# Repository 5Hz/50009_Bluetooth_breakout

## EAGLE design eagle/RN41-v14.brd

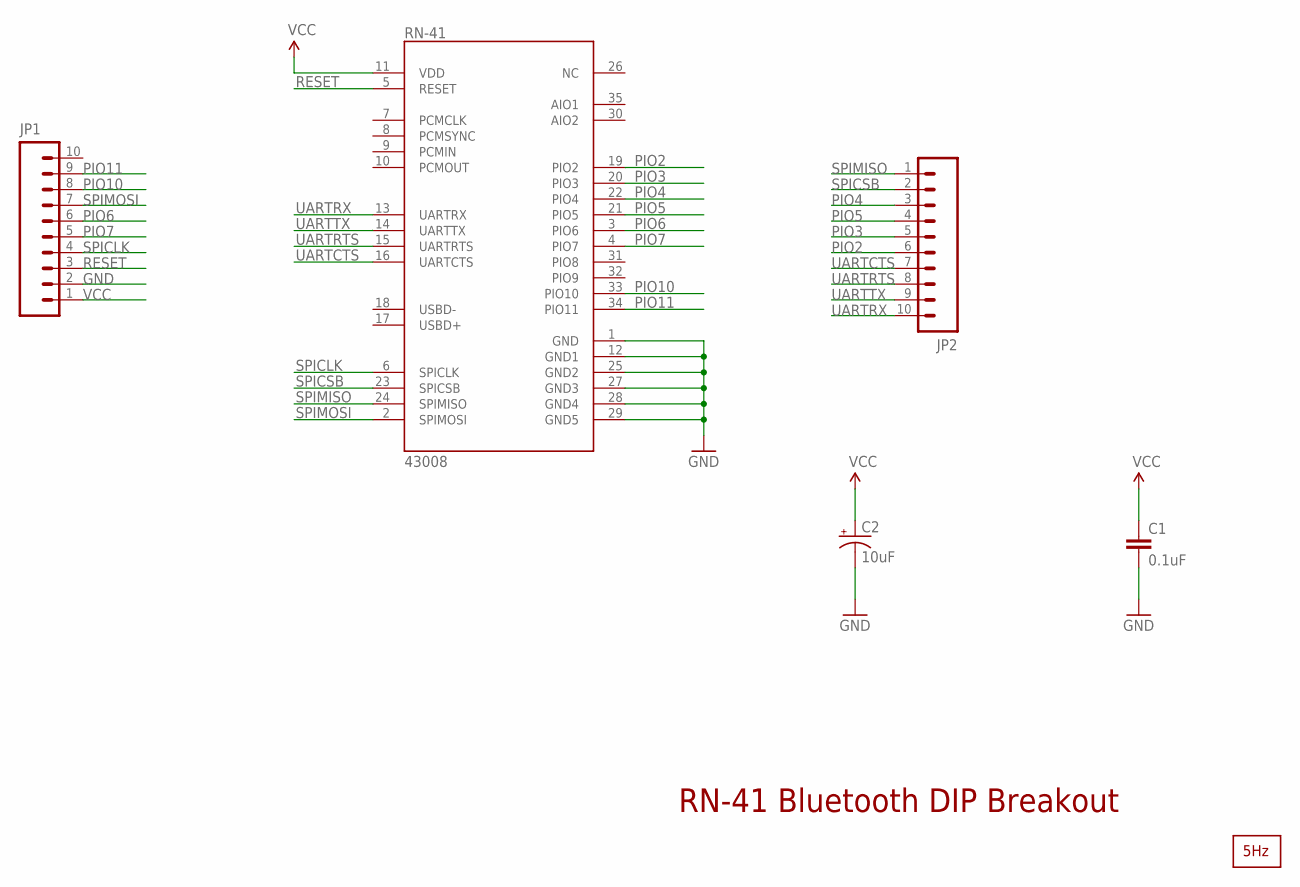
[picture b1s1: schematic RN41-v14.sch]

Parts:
C1: 0.1uF; 0603-CAP
C2: 10uF; EIA3216
JP1, JP2: M10"; 1X10
RN-41: 43008; RN41
U$1: LOGO2_SILKL10MM; LARGO2_10MM

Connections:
GND: C1.2, C2.C (-), JP1.2, RN-41.1 (GND), RN-41.12 (GND1), RN-41.25 (GND2), RN-41.27 (GND3), RN-41.28 (GND4), RN-41.29 (GND5)
PIO2: JP2.6, RN-41.19 (PIO2)
PIO3: JP2.5, RN-41.20 (PIO3)
PIO4: JP2.3, RN-41.22 (PIO4)
PIO5: JP2.4, RN-41.21 (PIO5)
PIO6: JP1.6, RN-41.3 (PIO6)
PIO7: JP1.5, RN-41.4 (PIO7)
PIO10: JP1.8, RN-41.33 (PIO10)
PIO11: JP1.9, RN-41.34 (PIO11)
RESET: JP1.3, RN-41.5 (RESET)
SPICLK: JP1.4, RN-41.6 (SPICLK)
SPICSB: JP2.2, RN-41.23 (SPICSB)
SPIMISO: JP2.1, RN-41.24 (SPIMISO)
SPIMOSI: JP1.7, RN-41.2 (SPIMOSI)
UARTCTS: JP2.7, RN-41.16 (UARTCTS)
UARTRTS: JP2.8, RN-41.15 (UARTRTS)
UARTRX: JP2.10, RN-41.13 (UARTRX)
UARTTX: JP2.9, RN-41.14 (UARTTX)
VCC: C1.1, C2.A (+), JP1.1, RN-41.11 (VDD)

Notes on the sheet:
RN-41 Bluetooth DIP Breakout

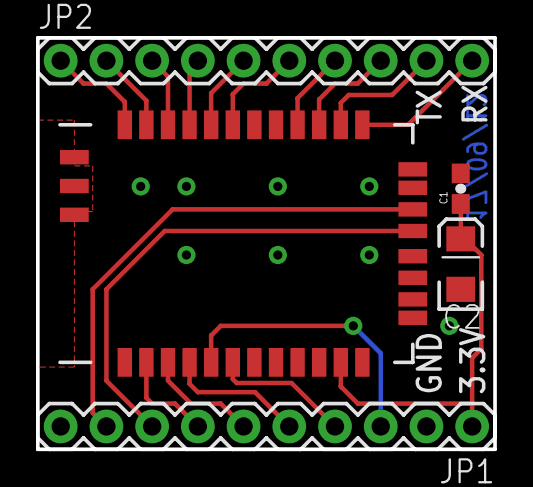
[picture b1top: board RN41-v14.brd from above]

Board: 2 copper layers, 25.4 x 22.9 mm, 6 parts (1 on the bottom side), 19 nets.

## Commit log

2014-01-09 creación
